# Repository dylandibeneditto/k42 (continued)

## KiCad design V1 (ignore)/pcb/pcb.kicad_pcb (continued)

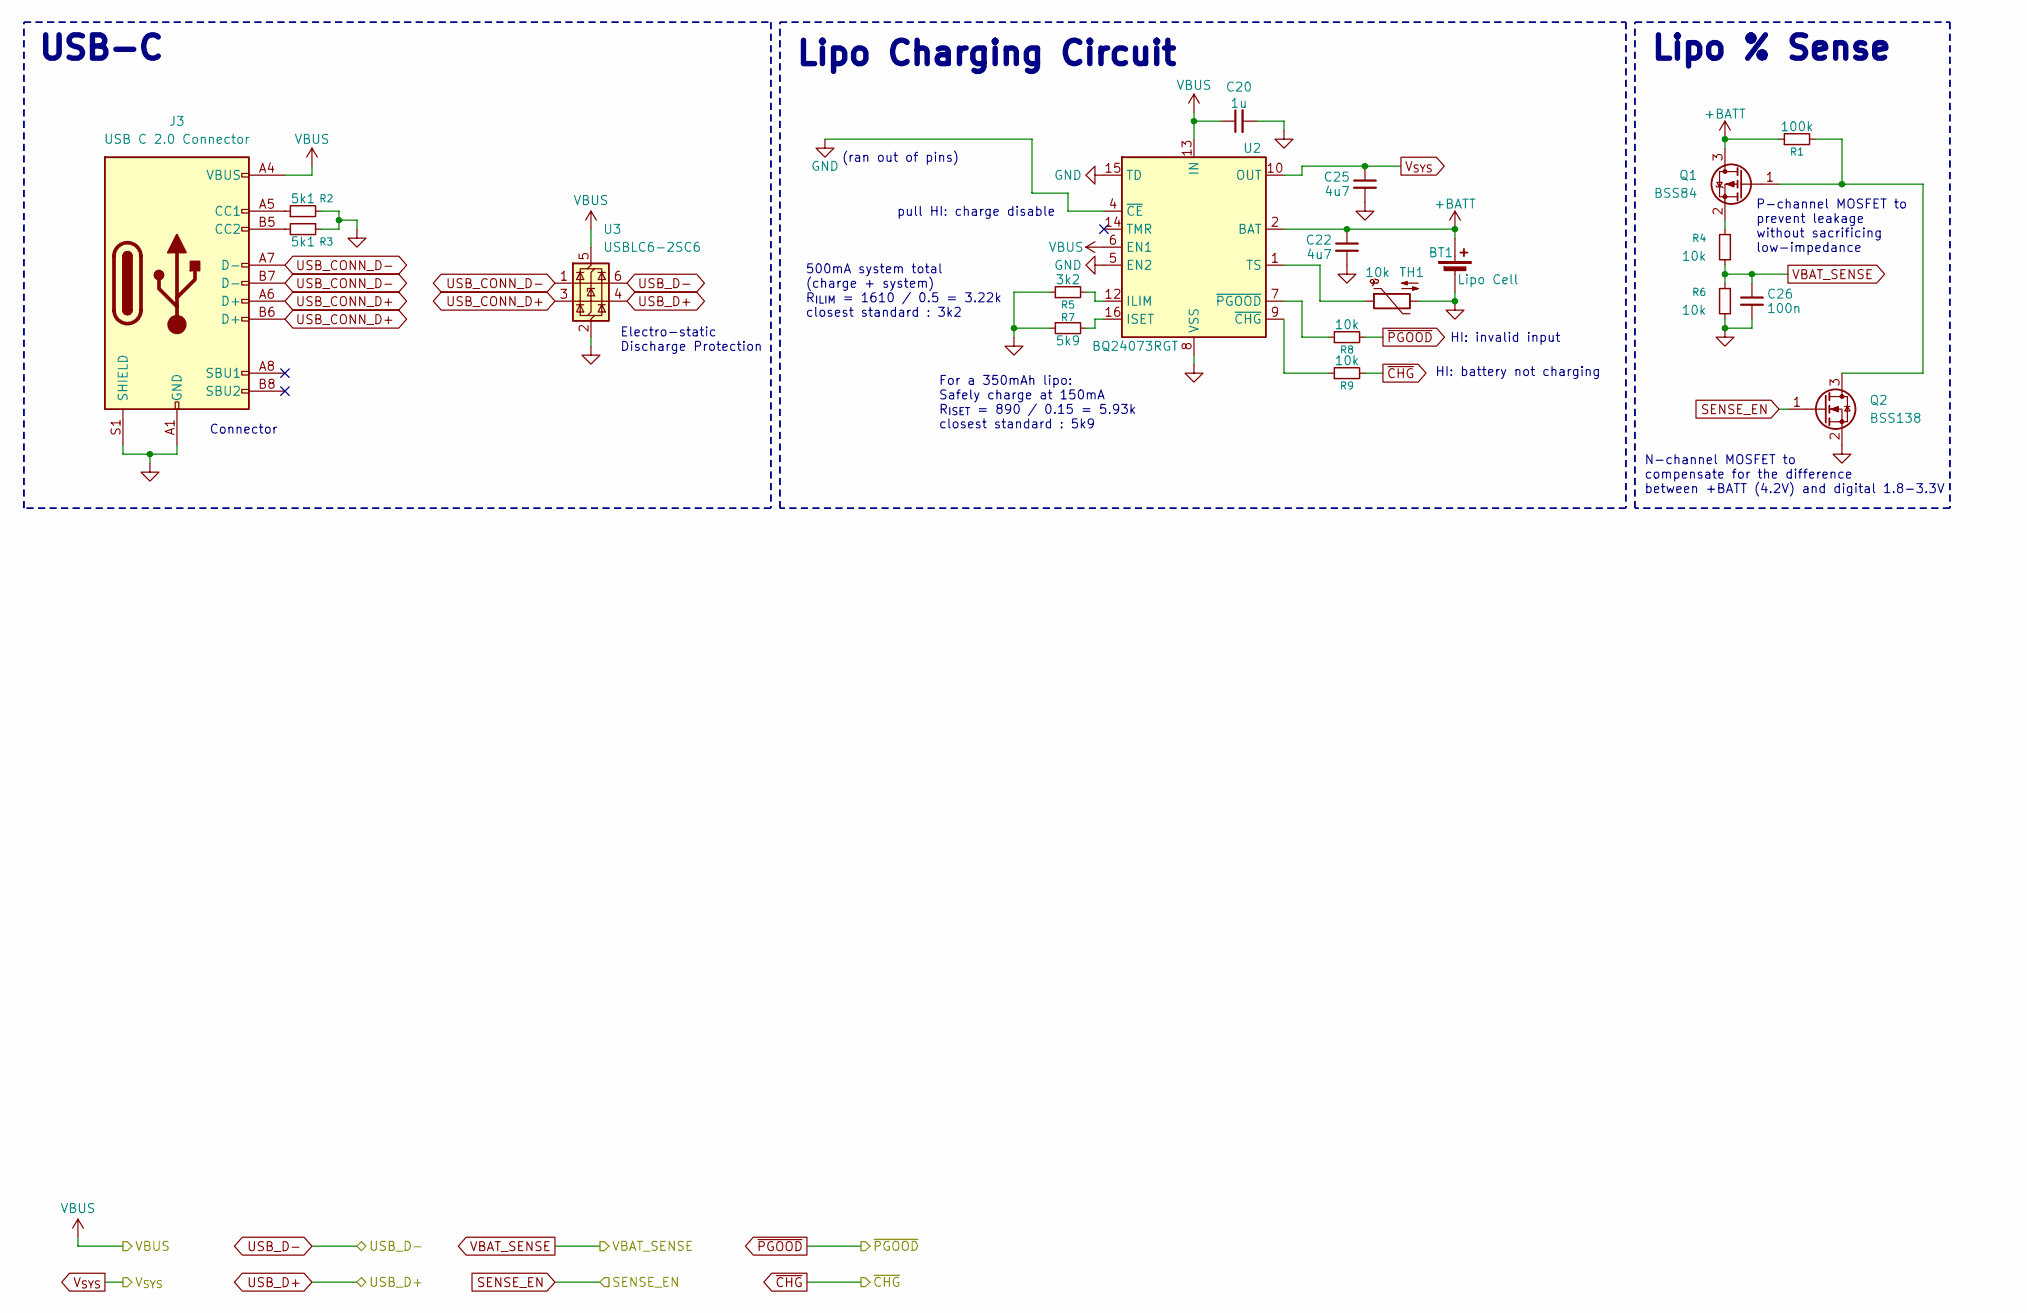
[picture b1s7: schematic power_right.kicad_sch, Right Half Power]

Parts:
BT1: Lipo Cell; JST_PH_S2B-PH-SM4-TB_1x02-1MP_P2.00mm_Horizontal; LCSC Part Number C295747
C20: 1u; C_0603_1608Metric; LCSC Part Number C15849
C22, C25: 4u7; C_0805_2012Metric; LCSC Part Number C1779
C26: 100n; C_0402_1005Metric; LCSC Part Number C1525
J3: USB C 2.0 Connector; TYPE-C-31-M-13C; LCSC Part Number C2765186
Q1: BSS84; SOT-23; LCSC Part Number C8492
Q2: BSS138; SOT-23; LCSC Part Number C8490
R1: 100k; R_0603_1608Metric; LCSC Part Number C25803
R2, R3: 5k1; R_0402_1005Metric; LCSC Part Number C17168
R4, R6, R8, R9: 10k; R_0402_1005Metric; LCSC Part Number C60490
R5: 3k2; R_0402_1005Metric; LCSC Part Number C705066
R7: 5k9; R_0402_1005Metric; LCSC Part Number C166634
TH1: 10k; R_0402_1005Metric; LCSC Part Number C209959
U2: BQ24073RGT; VQFN-16-1EP_3x3mm_P0.5mm_EP1.6x1.6mm; LCSC Part Number C15220
U3: USBLC6-2SC6; SOT-23-6; LCSC Part Number C2687116

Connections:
+BATT: BT1.1 (+), C22.1, Q1.3 (D), R1.1, U2.2 (BAT), U2.3 (BAT); also elsewhere on the board
GND: BT1.2 (-), C20.2, C22.2, C25.2, C26.2, J3.A1 (GND), J3.A12 (GND), J3.B1 (GND), J3.B12 (GND), J3.S1 (SHIELD), Q2.2 (S), R2.2, R3.1, R5.1, R6.2, R7.1, TH1.2, U2.4 (~CE), U2.5 (EN2), U2.8 (VSS), U2.15 (TD), U2.17 (VSS), U3.2 (GND); also elsewhere on the board
unnamed: J3.A5 (CC1), R2.1
unnamed: J3.B5 (CC2), R3.2
unnamed: Q1.1 (G), Q2.3 (D), R1.2
unnamed: Q1.2 (S), R4.1
unnamed: R5.2, U2.12 (ILIM)
unnamed: R7.2, U2.16 (ISET)
unnamed: TH1.1, U2.1 (TS)
unnamed: R9.1, U2.9 (~CHG)
unnamed: R8.1, U2.7 (~PGOOD)
SENSE_EN: Q2.1 (G); also elsewhere on the board
USB_CONN_D+: J3.A6 (D+), J3.B6 (D+), U3.3 (I/O2); also elsewhere on the board
USB_CONN_D-: J3.A7 (D-), J3.B7 (D-), U3.1 (I/O1); also elsewhere on the board
USB_D+: U3.4 (I/O2); also elsewhere on the board
USB_D-: U3.6 (I/O1); also elsewhere on the board
VBAT_SENSE: C26.1, R4.2, R6.1; also elsewhere on the board
VBUS: C20.1, J3.A4 (VBUS), J3.A9 (VBUS), J3.B4 (VBUS), J3.B9 (VBUS), U2.6 (EN1), U2.13 (IN), U3.5 (VBUS); also elsewhere on the board
V_{SYS}: C25.1, U2.10 (OUT), U2.11 (OUT); also elsewhere on the board
~CHG: R9.2; also elsewhere on the board
~PGOOD: R8.2; also elsewhere on the board

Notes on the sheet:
Connector
HI: battery not charging
P-channel MOSFET to prevent leakage without sacrificing low-impedance
Electro-static Discharge Protection
Lipo % Sense
N-channel MOSFET to compensate for the difference between +BATT (4.2V) and digital 1.8-3.3V
USB-C
HI: invalid input
500mA system total (charge + system) R_{ILIM} = 1610 / 0.5 = 3.22k closest standard : 3k2
(ran out of pins)
For a 350mAh lipo: Safely charge at 150mA R_{ISET} = 890 / 0.15 = 5.93k closest standard : 5k9
Lipo Charging Circuit
pull HI: charge disable

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
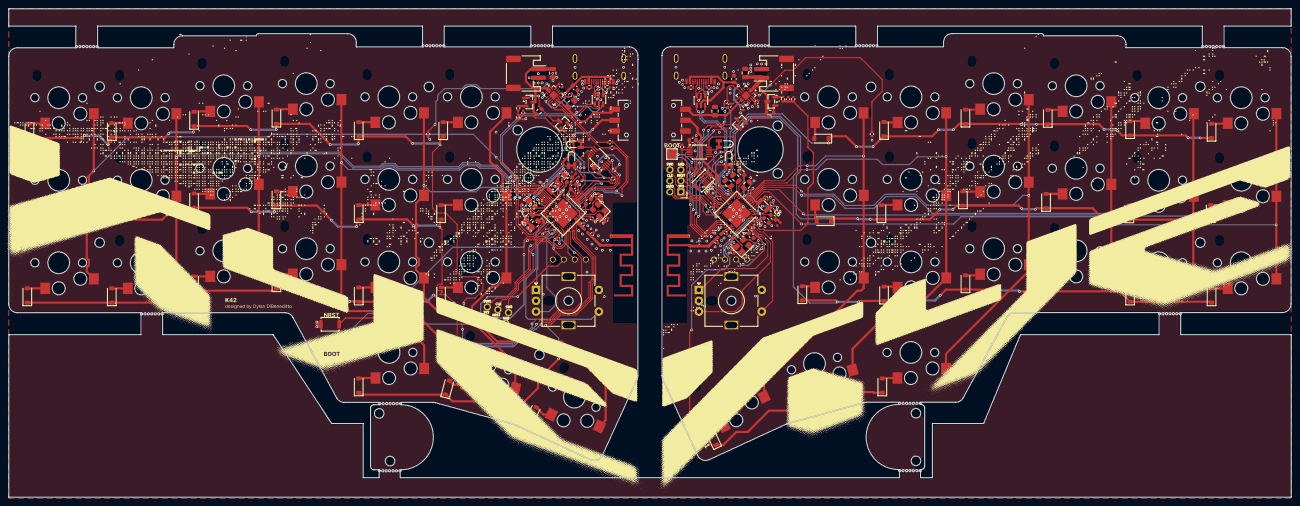
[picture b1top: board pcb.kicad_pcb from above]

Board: 2 copper layers, 296.0 x 112.7 mm, 208 parts (1 on the bottom side), 130 nets.

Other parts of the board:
U4#2: DRV2605LDGS; VSSOP-10_3x3mm_P0.5mm

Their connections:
/Right/LRA_A: U4#2.7 (OUT+); also elsewhere on the board
/Right/LRA_B: U4#2.9 (OUT-); also elsewhere on the board
GND: U4#2.4 (IN/TRIG), U4#2.8 (GND); also elsewhere on the board
HAPTIC_EN: U4#2.5 (EN); also elsewhere on the board
HAPTIC_SCL: U4#2.2 (SCL); also elsewhere on the board
HAPTIC_SDA: U4#2.3 (SDA); also elsewhere on the board
VDD: U4#2.10 (VDD); also elsewhere on the board

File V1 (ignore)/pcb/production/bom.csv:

Designator,Footprint,Quantity,Value,LCSC Part #
"AE1, AE2",BLE_ANTENNA,2,Antenna_Shield,
"BT1, BT3",JST_PH_S2B-PH-SM4-TB_1x02-1MP_P2.00mm_Horizontal,2,Lipo Cell,
"C1, C2, C3, C33, C34, C36, C37, C4",0402,8,8p,
"C10, C17, C22, C25, C45, C47, C52, C54, C55, C6",0805,10,4u7,
"C11, C13, C16, C26, C38, C49, C5, C50, C51, C56",0402,10,100n,
"C14, C42",0402,2,47n,
"C15, C20, C24, C43, C46, C48, C53, C8",0603,8,1u,
"C18, C32",0402,2,0.5pF,
"C19, C35",0402,2,0.8pF,
"C40, C9",0402,2,100p,
"D1, D10, D11, D12, D13, D14, D15, D16, D17, D18, D19, D2, D20, D21, D3, D4, D43, D44, D45, D46, D47, D48, D49, D5, D50, D51, D52, D53, D54, D55, D56, D57, D58, D59, D6, D60, D61, D62, D63, D7, D8, D9",D_SOD-123,42,1N4148W,
"J1, J7",OLED,2,OLED Connector,
"J10, J2",PinHeader_2x03_P2.54mm_Vertical,2,Tag connect TC2030-CTX,
"J11, J3",TYPE-C-31-M-13C,2,USB C 2.0 Connector,
"J4, J5, J8, J9",TE_2199248-6,4,Conn_01x01_Socket,C3308715
"L1, L3, L6, L7",0603,4,10uH,
"L2, L8",0402,2,15nH,
"L4, L5",0402,2,4.7nH,
"Q1, Q5",SOT-23,2,BSS84,
"Q2, Q6",SOT-23,2,BSS138,
"R1, R23",0603,2,100k,
"R10, R11, R21, R22",0402,4,2k2,
"R2, R24, R25, R3",0402,4,5k1,
"R26, R28, R30, R31, R4, R6, R8, R9",0402,8,10k,
"R27, R5",0402,2,3k2,
"R29, R7",0402,2,5k9,
"SW1, SW46",SW_Push_SPST_NO_Alps_SKRK,2,RESET,C720477
"SW10, SW11, SW12, SW13, SW14, SW15, SW16, SW17, SW18, SW19, SW2, SW20, SW21, SW22, SW3, SW4, SW49, SW5, SW50, SW51, SW52, SW53, SW54, SW55, SW56, SW57, SW58, SW59, SW6, SW60, SW61, SW62, SW63, SW64, SW65, SW66, SW67, SW68, SW69, SW7, SW8, SW9",keyswitch_choc12_hotswap_1u,42,SW_Push,
"SW23, SW48",RotaryEncoder_Alps_EC11E-Switch_Vertical_H20mm_MountingHoles,2,EC11 Encoder,
"SW24, SW47",SW_SPDT_CK_JS102011SAQN,2,ON/OFF,C49023767
"TH1, TH3",0402,2,10k,C209959
"TP1, TP2",TestPoint_Pad_2.0x2.0mm,2,TestPoint,
"U1, U7",Nordic_AQFN-73-1EP_7x7mm_P0.5mm,2,nRF52840,
"U10, U3",SOT-23-6,2,USBLC6-2SC6,
"U2, U9",VQFN-16-1EP_3x3mm_P0.5mm_EP1.6x1.6mm,2,BQ24073RGT,
"U4_2, U4",VSSOP-10_3x3mm_P0.5mm,2,DRV2605LDGS,
"Y1, Y3",Crystal_SMD_3225-4Pin_3.2x2.5mm,2,32MHz,C2149125
"Y2, Y4",Crystal_SMD_3215-2Pin_3.2x1.5mm,2,32.768kHz,C32346

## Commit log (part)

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2026-06-23 initial nRF52840 design
